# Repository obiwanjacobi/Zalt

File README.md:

# Zalt

Zalt is a home brew Z80 computer with a modern(isch) chipset.

## Zalt Z80 Computer

| Made by Marc Jacobi 2016-2020 |
| --- |
| blog: https://jacobielectronix.wordpress.com/category/zalt/
| email: obiwanjacobi@hotmail.com

<br/>

| Modules: | |
| --- | --- |
| CPU Board | (v1.0) |
| Decoder Board | (v1.0) |
| BusSpy Board | (no pcb) |

<br/>

| Folders: |   |
| --- | --- |
| BusSpy Board | module (handwired)
| CPU Board v1.0 - locked | module (in production)
| Decoder Board v1.0 - locked | module (in production)
| VDP Board v1.0 - locked | module (in production)
| Design | braindump and design documents
| Kicad | Zalt specific (shared) libraries
| Kicad/Board Template | PCB template for stackable boards.
| Kicad/Logical Design | Logical scratch pad for working on ideas.
| Source | Zalt OS source code
| Source/Jacobi.Zalt.IntegrationTests | Zim80 tests
| Source/SystemController | PSoC5 project and source code
| Source/Z80 Tests | Location for all kinds of test code
| Source/Zalt Bios | The Zalt OS source code (to be moved)
| Source/z88dk target | Source for the z88dk Zalt target
| Under Construction/GPU Board v0.1 | Graphics based on a ARM MCU
| Under Construction/TTL VGA v.01 | Graphics with TTL/GAL 1st prototype (partially build)
| Under Construction/TTL VGA v.02 | Graphics with TTL/GAL 2nd prototype
| Under Construction/ZaltToISA | PC ISA interfacing

<br/>

Disclaimer: Only at a very basic level does any of the BIOS code work - see tests. A lot of the source code is still being developed (and changed).

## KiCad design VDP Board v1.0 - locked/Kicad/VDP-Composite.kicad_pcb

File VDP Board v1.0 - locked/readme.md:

# Zalt Video and Audio

This Board contains the V9958 (video) and a YM2149 (sound) vintage chips.
It contains the full set of DRAMs for the V9958, that is a VRAM of 128kB and an extra 64kB extension.

The video signals are available on an IDC connector with grounds separating each signal. RGB and Composite video as well as Chroma and Luma (s-video) signals are present. Note that this is not VGA! Also the stereo Audio is available on this connector.

The YM2149 generates 3 channels of sound which are mixed into a stereo audio output. It also exposes 2 8-bit IO-ports which are brought out on the Audio/Video header.

In addition the board contains a register to hold an RST instruction for Interrupt Mode 0 or an Interrupt Vector for Mode 2 that can be set in software and is put on the bus when an interrupt acknowledge is detected. A jumper can be switched to enable/disable (for IM1 for instance) this option. The interrupt is optionally generated by the V9958.

## TODO

- Too late: I probably need the `INT` signal from the V9958 in the GAL to decide if to handle the the interrupt and (optionally) put the vector on the bus. 1 bodge-wire should fix that. There is still a potential issue with the existing code in the System Controller that also handles interrupts.

## Credits

All credits for the schematic go to these projects.

The V9958 circuit has been copied from the MSX clone project Omega.
https://github.com/skiselev/omega

The YM2149 circuit was copied from this YM2149 for the RC2014 project. https://github.com/electrified/rc2014-ym2149
(although I only used the channel mixing resistors)

## Resources

V9938 Programming Guide (pdf)

Several articles on VDP programming and sources: 
http://map.grauw.nl/articles/vdp_tut.php
http://map.grauw.nl/sources/vdp_rout.php

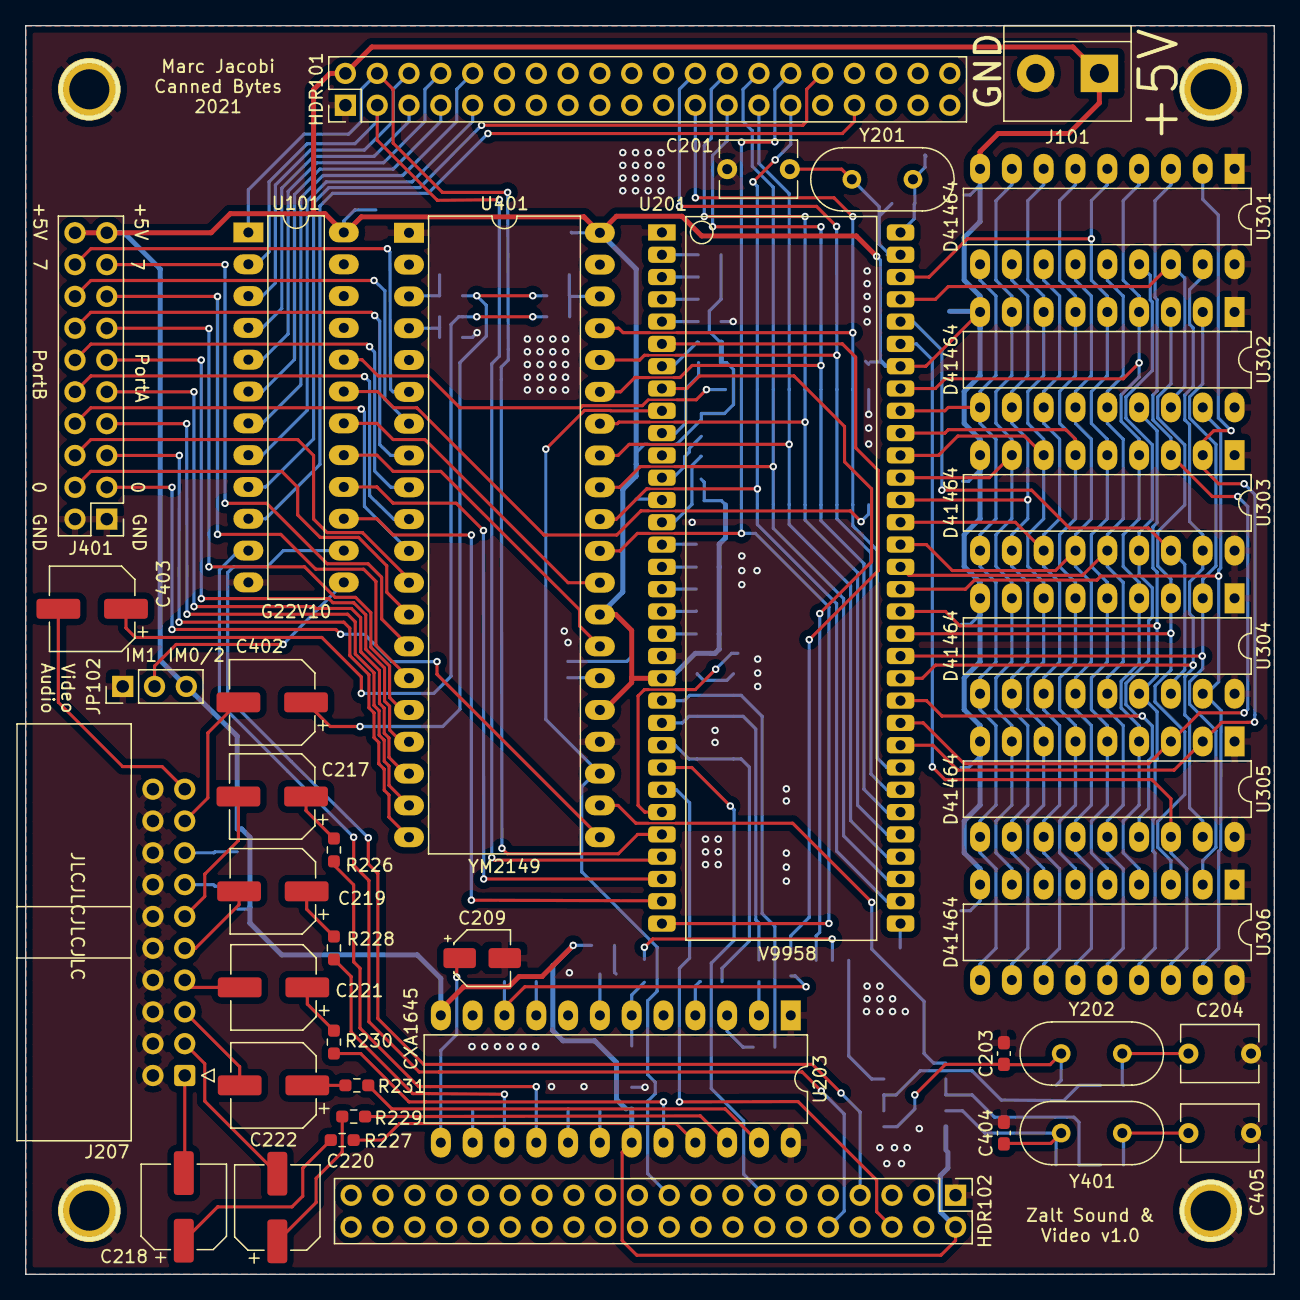
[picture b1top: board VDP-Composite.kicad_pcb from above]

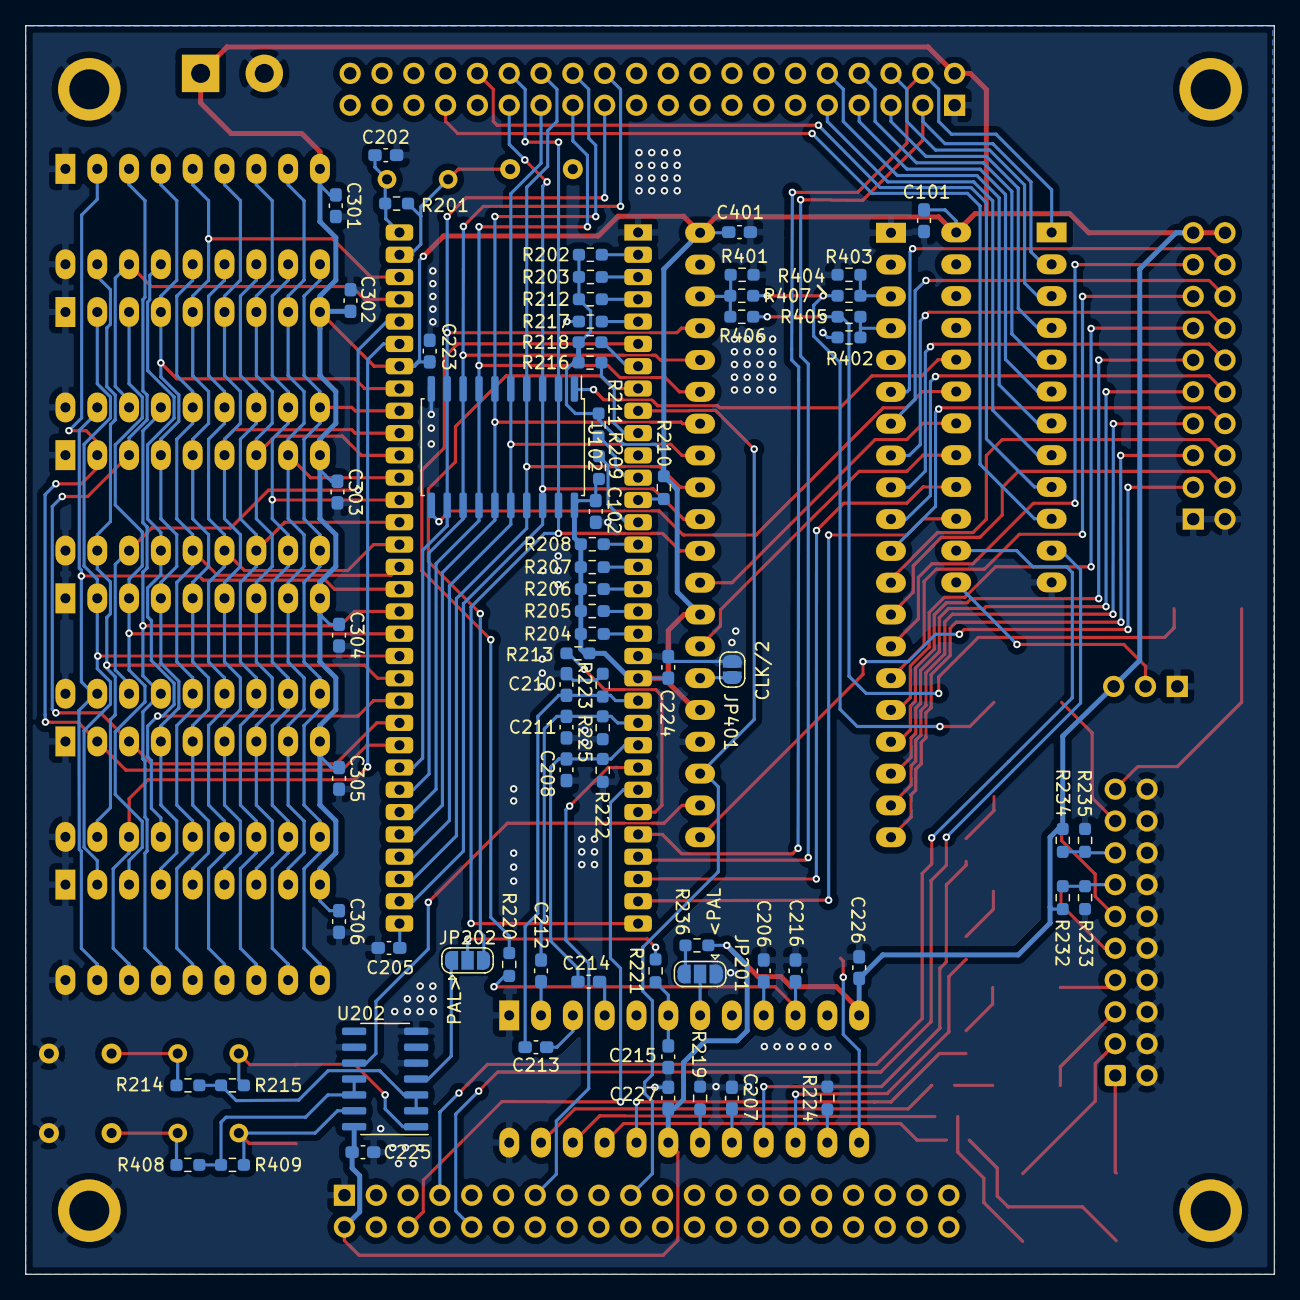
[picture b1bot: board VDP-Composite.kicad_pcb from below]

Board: 2 copper layers, 99.7 x 99.7 mm, 113 parts (70 on the bottom side), 141 nets.

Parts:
1PIN, 1PIN#2, 1PIN#3, 1PIN#4: P***; 1pin
C101, C102, C205, C206, C208, C210, C211, C212, C213, C214, C223, C224, C225, C226, C227, C301, C302, C303, C304, C305, C306, C401: 100nF; C_0603_1608Metric_Pad1.08x0.95mm_HandSolder
C201, C204, C405: 30pF; C_Disc_D6.0mm_W4.4mm_P5.00mm
C202, C203, C404: 22pF; C_0603_1608Metric_Pad1.08x0.95mm_HandSolder
C207: *27/18pF; C_0603_1608Metric_Pad1.08x0.95mm_HandSolder
C209: 10uF; CP_Elec_4x3
C215: 4.7pF; C_0603_1608Metric_Pad1.08x0.95mm_HandSolder
C216: 47pF; C_0603_1608Metric_Pad1.08x0.95mm_HandSolder
C217, C218, C219, C220, C221, C222, C402, C403: 220uF; CP_Elec_6.3x7.7
HDR101: BUSHDR-A; PinHeader_2x20_P2.54mm_Vertical
HDR102: BUSHDR-B; PinHeader_2x20_P2.54mm_Vertical
J101: Power +5V; TerminalBlock_bornier-2_P5.08mm
J207: AVConn; IDC-Header_2x10_P2.54mm_Horizontal
J401: Ports; PinHeader_2x10_P2.54mm_Vertical
JP102: EnableIM; PinHeader_1x03_P2.54mm_Vertical
JP201, JP202: NTSC/PAL; SolderJumper-3_P1.3mm_Open_RoundedPad1.0x1.5mm
JP401: Clock/2; SolderJumper-2_P1.3mm_Open_RoundedPad1.0x1.5mm
R201: 470k; R_0603_1608Metric_Pad0.98x0.95mm_HandSolder
R202, R203, R204, R205, R206, R207, R208, R209, R210, R211, R212, R213, R216, R218, R233: 10k; R_0603_1608Metric_Pad0.98x0.95mm_HandSolder
R214, R220, R232, R236, R406, R407, R408: 1k; R_0603_1608Metric_Pad0.98x0.95mm_HandSolder
R215, R409: 1M; R_0603_1608Metric_Pad0.98x0.95mm_HandSolder
R217, R222, R223, R225: 470; R_0603_1608Metric_Pad0.98x0.95mm_HandSolder
R219: *20/16k; R_0603_1608Metric_Pad0.98x0.95mm_HandSolder
R221: 2.2k; R_0603_1608Metric_Pad0.98x0.95mm_HandSolder
R224: 47k; R_0603_1608Metric_Pad0.98x0.95mm_HandSolder
R226, R227, R228, R229, R230, R231: 75; R_0603_1608Metric_Pad0.98x0.95mm_HandSolder
R234: 120; R_0603_1608Metric_Pad0.98x0.95mm_HandSolder
R235: 180; R_0603_1608Metric_Pad0.98x0.95mm_HandSolder
R401, R402, R403: 3k; R_0603_1608Metric_Pad0.98x0.95mm_HandSolder
R404, R405: 1k6; R_0603_1608Metric_Pad0.98x0.95mm_HandSolder
U101: G22V10; DIP-24_W7.62mm_LongPads
U102: 74HCT574; SOIC-20W_7.5x12.8mm_P1.27mm
U201: V9958; DIP-64_1.78mm_W19.05mm
U202: 74HCT04; SOIC-14_3.9x8.7mm_P1.27mm
U203: CXA1645; DIP-24_W10.16mm_LongPads
U301, U302, U303, U304, U305, U306: D41464; DIP-18_W7.62mm_LongPads
U401: YM2149; DIP-40_W15.24mm_LongPads
Y201: 21.47727MHz; Crystal_HC49-4H_Vertical
Y202: 4.433618MHz; Crystal_HC49-4H_Vertical
Y401: 2-4MHz; Crystal_HC49-4H_Vertical

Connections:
+5V: C101.1, C102.1, C223.1, C224.1, C225.1, C226.1, C227.1, C301.1, C302.1, C303.1, C304.1, C305.1, C306.1, C401.2, HDR101.2, HDR102.2, J101.1, J401.19, J401.20, JP102.3, R202.1, R203.1, R204.1, R205.1, R206.1, R207.1, R208.1, R209.1, R210.1, R211.1, R212.1, R213.1, R216.1, R218.1, R232.1, R234.1, R236.1, U101.24, U102.20, U201.21, U201.58, U202.14, U203.12, U203.19, U301.9, U302.9, U303.9, U304.9, U305.9, U306.9, U401.25, U401.28, U401.40
/A0: HDR101.3, U101.2, U201.29
/A1: HDR101.4, U101.1, U201.28
/A2: HDR101.5, U101.4
/A3: HDR101.6, U101.3
/A4: HDR101.7, U101.6
/A5: HDR101.8, U101.5
/A6: HDR101.9, U101.8
/A7: HDR101.10, U101.7
/BC1: U101.18, U401.29
/BDIR: U101.17, U401.27
/D0: HDR101.23, U102.9, U102.12, U201.40, U401.37
/D1: HDR101.24, U102.8, U102.13, U201.39, U401.36
/D2: HDR101.25, U102.7, U102.14, U201.38, U401.35
/D3: HDR101.26, U102.6, U102.15, U201.37, U401.34
/D4: HDR101.27, U102.5, U102.16, U201.36, U401.33
/D5: HDR101.28, U102.4, U102.17, U201.35, U401.32
/D6: HDR101.29, U102.3, U102.18, U201.34, U401.31
/D7: HDR101.30, U102.2, U102.19, U201.32, U401.30
/IVL: U101.19, U102.11
/SoundGen/A: R403.2, R404.2, U401.3
/SoundGen/AudioL: C402.2, J207.17
/SoundGen/AudioR: C403.2, J207.19
/SoundGen/B: R402.2, R405.2, U401.4
/SoundGen/C: R401.2, R406.2, R407.2, U401.38
/SoundGen/CLK: U202.10, U401.22
/VDP/AV: J207.13, R232.2, R233.1
/VDP/BLUE: C222.2, J207.5
/VDP/Bin: C208.1, C214.2, R222.1, U201.24
/VDP/Bout: C214.1, U203.4
/VDP/CAR-NTSC: JP202.3, U201.8
/VDP/CAR-PAL: JP202.1, U202.4
/VDP/CARout: C215.1, R221.2, U203.6
/VDP/CHROMA: C219.2, J207.9
/VDP/COMP: C221.2, J207.7
/VDP/GREEN: C220.2, J207.3
/VDP/Gin: C210.1, C213.2, R223.1, U201.22
/VDP/Gout: C213.1, U203.3
/VDP/LUMA: C217.2, J207.11
/VDP/RED: C218.2, J207.1
/VDP/Rin: C211.1, C212.2, R225.1, U201.23
/VDP/Rout: C212.1, U203.2
/VDP/SYNCin: R220.1, U201.6
/VDP/SYNCout: C216.1, R220.2, U203.10
/VDP/VRAM/AD0: U201.49, U301.14, U302.14, U303.14, U304.14, U305.14, U306.14
/VDP/VRAM/AD1: U201.50, U301.13, U302.13, U303.13, U304.13, U305.13, U306.13
/VDP/VRAM/AD2: U201.51, U301.12, U302.12, U303.12, U304.12, U305.12, U306.12
/VDP/VRAM/AD3: U201.52, U301.11, U302.11, U303.11, U304.11, U305.11, U306.11
/VDP/VRAM/AD4: U201.53, U301.8, U302.8, U303.8, U304.8, U305.8, U306.8
/VDP/VRAM/AD5: U201.54, U301.7, U302.7, U303.7, U304.7, U305.7, U306.7
/VDP/VRAM/AD6: U201.55, U301.6, U302.6, U303.6, U304.6, U305.6, U306.6
/VDP/VRAM/AD7: U201.56, U301.10, U302.10, U303.10, U304.10, U305.10, U306.10
/VDP/VRAM/RD0: U201.41, U301.2, U303.2, U305.2
/VDP/VRAM/RD1: U201.42, U301.3, U303.3, U305.3
/VDP/VRAM/RD2: U201.43, U301.15, U303.15, U305.15
/VDP/VRAM/RD3: U201.44, U301.17, U303.17, U305.17
/VDP/VRAM/RD4: U201.45, U302.2, U304.2, U306.2
/VDP/VRAM/RD5: U201.46, U302.3, U304.3, U306.3
/VDP/VRAM/RD6: U201.47, U302.15, U304.15, U306.15
/VDP/VRAM/RD7: U201.48, U302.17, U304.17, U306.17
/VDP/VRAM/R~W: U201.57, U301.4, U302.4, U303.4, U304.4, U305.4, U306.4
/VDP/VRAM/~CAS1: U201.61, U301.16, U302.16
/VDP/VRAM/~CAS2: U201.60, U303.16, U304.16
/VDP/VRAM/~CASx: U201.59, U305.16, U306.16
/VDP/VRAM/~RAS: U201.62, U301.5, U302.5, U303.5, U304.5, U305.5, U306.5
/VDP/YS: J207.15, R234.2, R235.1
/~INT: HDR102.13, U201.25
/~IOREQ: HDR102.10, U101.11
/~IVOE: U101.20, U102.1
/~M1: HDR102.7, U101.14
/~RD: HDR101.33, U101.10
/~RST: HDR102.19, U201.9, U401.23
/~VDP_RD: U101.15, U201.31
/~VDP_WR: U101.16, U201.30
/~WAIT: HDR102.6, U201.26
/~WR: HDR101.32, U101.9
GND: 1PIN.1, 1PIN#2.1, 1PIN#3.1, 1PIN#4.1, C101.2, C102.2, C201.2, C202.2, C203.2, C204.2, C205.2, C206.2, C207.2, C208.2, C209.2, C210.2, C211.2, C215.2, C216.2, C223.2, C224.2, C225.2, C226.2, C227.2, C301.2, C302.2, C303.2, C304.2, C305.2, C306.2, C401.1, C404.2, C405.2, HDR101.1, HDR102.1, J101.2, J207.2, J207.4, J207.6, J207.8, J207.10, J207.12, J207.14, J207.16, J207.18, J207.20, J401.1, J401.2, JP102.1, JP201.1, JP401.1, R217.2, R219.2, R222.2, R223.2, R224.2, R225.2, R233.2, R235.2, R401.1, R402.1, R403.1, U101.12, U102.10, U201.1, U201.20, U202.5, U202.7, U202.9, U203.1, U203.24, U301.1, U301.18, U302.1, U302.18, U303.1, U303.18, U304.1, U304.18, U305.1, U305.18, U306.1, U306.18, U401.1, U401.24
unnamed: C201.1, R201.1, U201.63, Y201.1
unnamed: C202.1, R201.2, U201.64, Y201.2
unnamed: C203.1, R215.1, U202.1, Y202.1
unnamed: C204.1, R214.2, Y202.2
unnamed: C205.1, U201.33
unnamed: C206.1, U203.9
unnamed: C207.1, U203.17
unnamed: C209.1, U203.13
unnamed: C217.1, R226.2
unnamed: C218.1, R227.2
unnamed: C219.1, R228.2
unnamed: C220.1, R229.2
unnamed: C221.1, R230.2
unnamed: C222.1, R231.2
unnamed: C402.1, R404.1, R407.1
unnamed: C403.1, R405.1, R406.1
unnamed: C404.1, R409.1, U202.13, Y401.1
unnamed: C405.1, R408.2, Y401.2
unnamed: J401.3, U401.21
unnamed: J401.4, U401.13
unnamed: J401.5, U401.20
unnamed: J401.6, U401.12
unnamed: J401.7, U401.19
unnamed: J401.8, U401.11
unnamed: J401.9, U401.18
unnamed: J401.10, U401.10
unnamed: J401.11, U401.17
unnamed: J401.12, U401.9
unnamed: J401.13, U401.16
unnamed: J401.14, U401.8
unnamed: J401.15, U401.15
unnamed: J401.16, U401.7
unnamed: J401.17, U401.14
unnamed: J401.18, U401.6
unnamed: JP102.2, U101.13
unnamed: JP201.2, U203.7
unnamed: JP201.3, R236.2
unnamed: JP202.2, R221.1
unnamed: JP401.2, U401.26
unnamed: R202.2, U201.2
unnamed: R203.2, U201.3
unnamed: R204.2, U201.19
unnamed: R205.2, U201.18
unnamed: R206.2, U201.17
unnamed: R207.2, U201.16
unnamed: R208.2, U201.15
unnamed: R209.2, U201.14
unnamed: R210.2, U201.13
unnamed: R211.2, U201.12
unnamed: R212.2, U201.4
unnamed: R213.2, U201.27
unnamed: R214.1, R215.2, U202.2, U202.3
unnamed: R216.2, U201.10
unnamed: R217.1, U201.5
unnamed: R218.2, U201.7
unnamed: R219.1, U203.18
unnamed: R224.1, U203.14
unnamed: R226.1, U203.16
unnamed: R227.1, U203.21
unnamed: R228.1, U203.15
unnamed: R229.1, U203.22
unnamed: R230.1, U203.20
unnamed: R231.1, U203.23
unnamed: R408.1, R409.2, U202.11, U202.12

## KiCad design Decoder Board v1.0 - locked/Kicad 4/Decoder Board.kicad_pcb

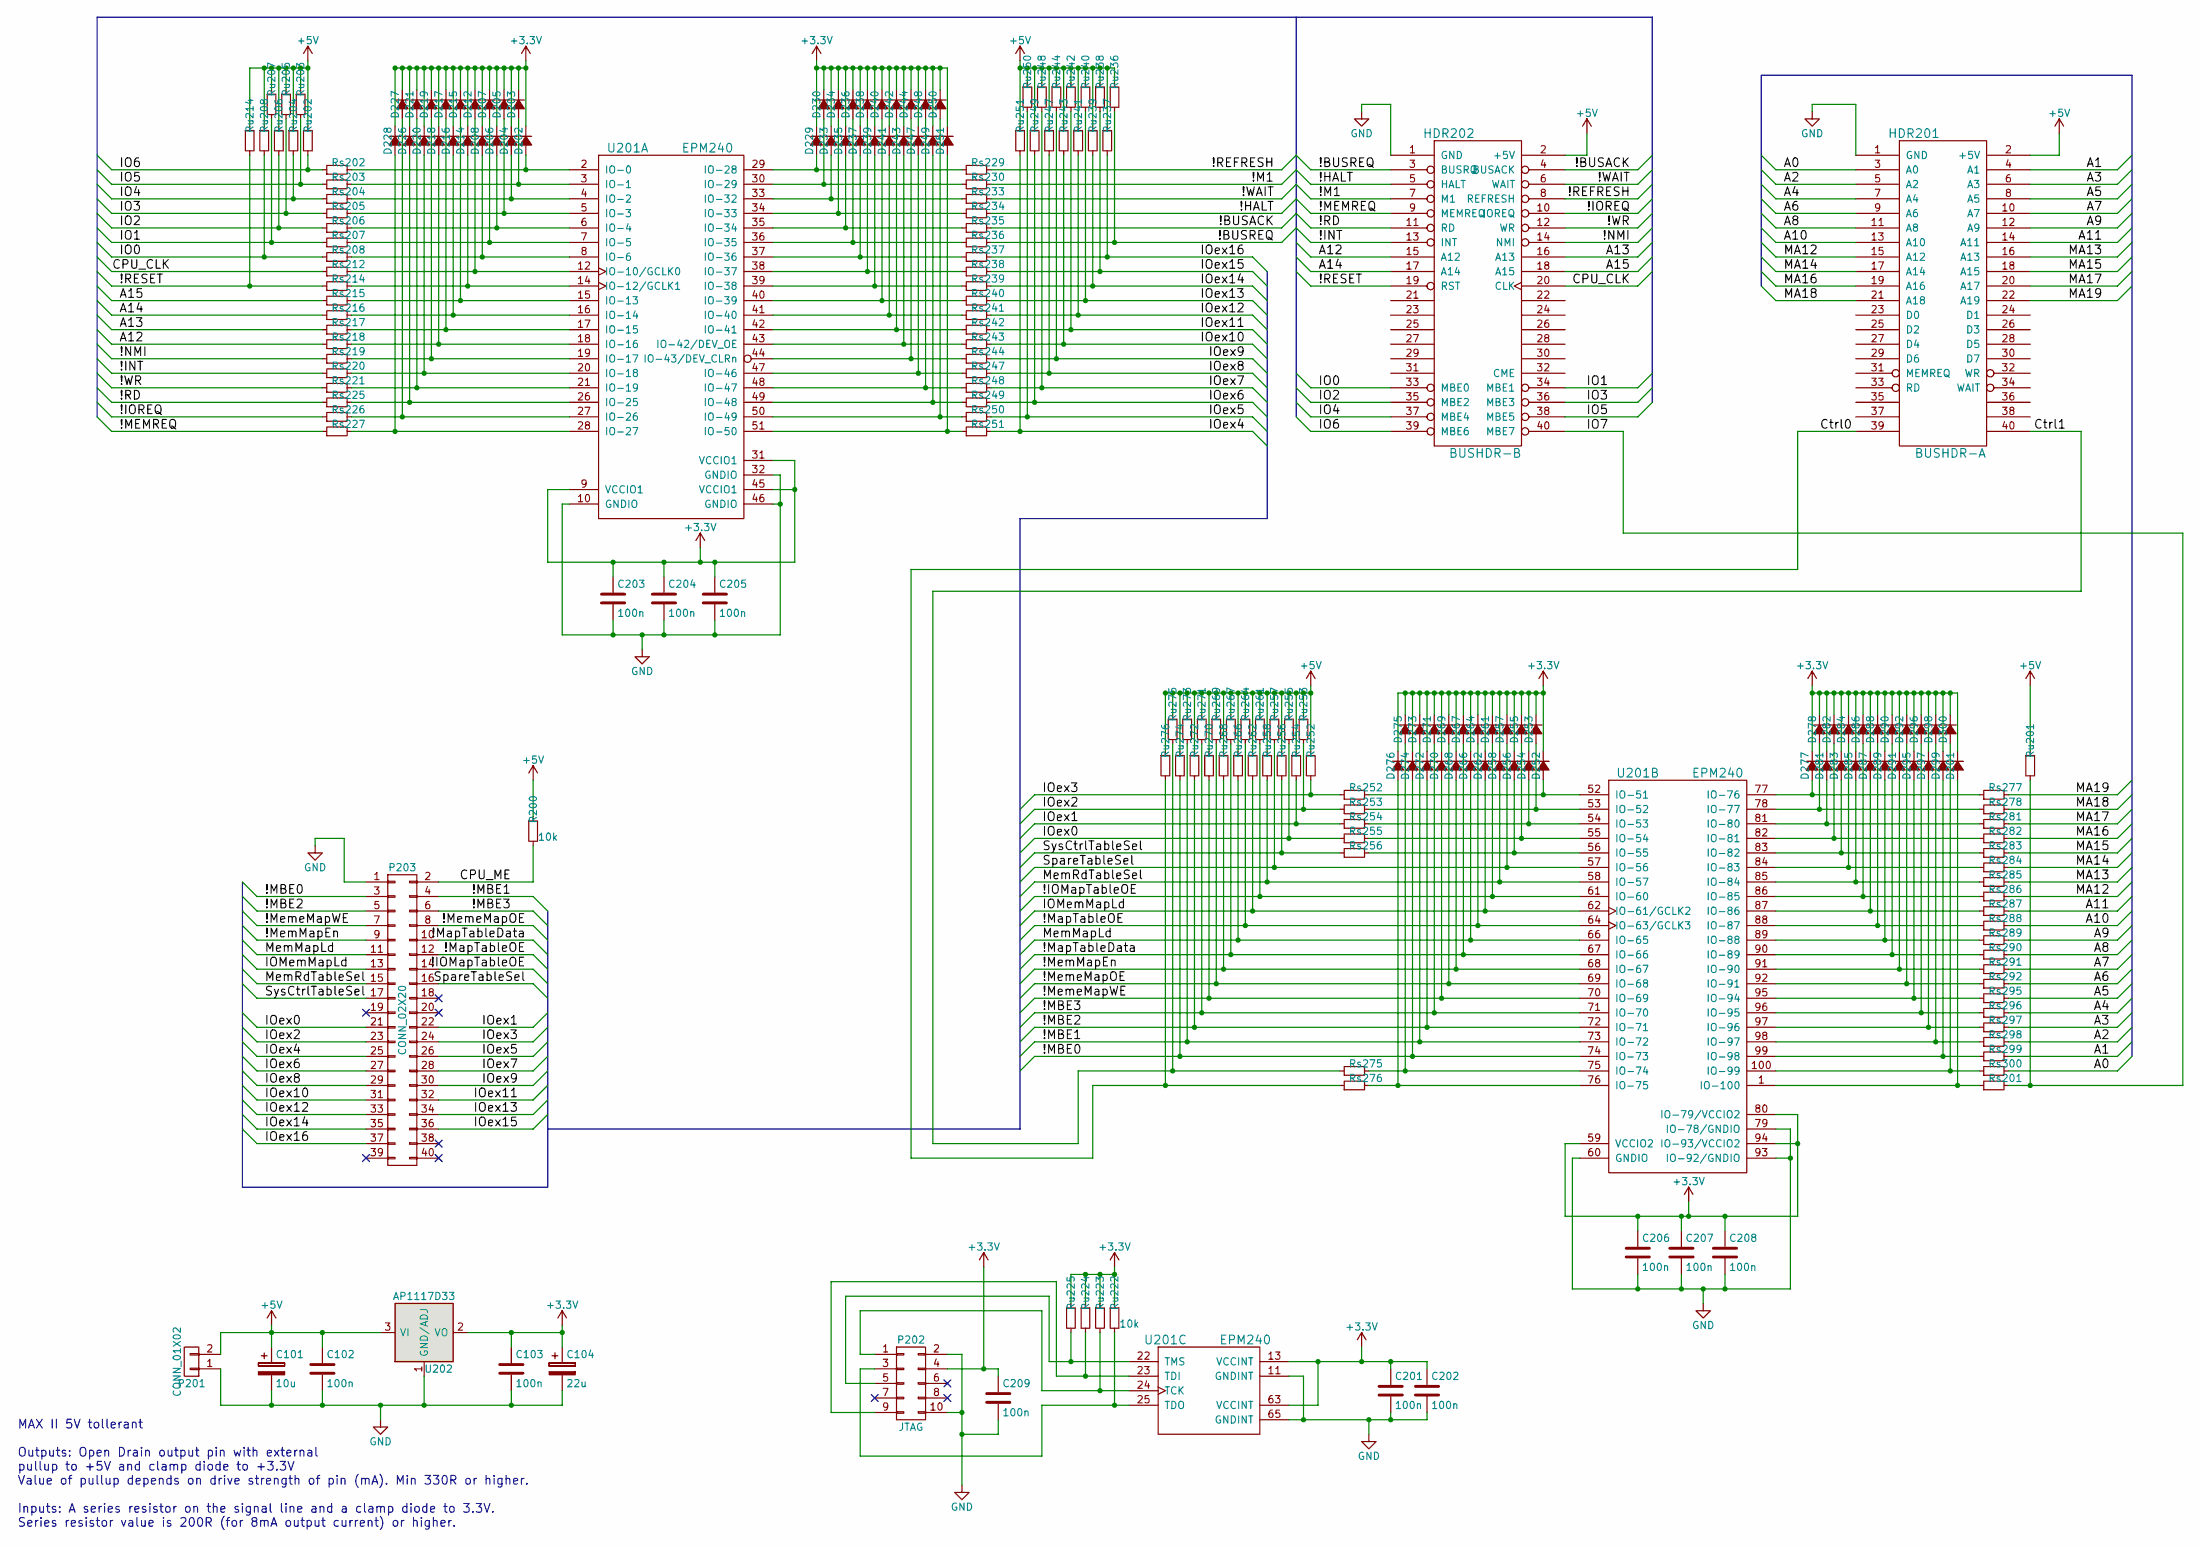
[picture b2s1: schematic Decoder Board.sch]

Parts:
C101: 10u; TantalC_SizeC_EIA-6032_HandSoldering
C102, C103, C201, C202, C203, C204, C205, C206, C207, C208, C209: 100n; C_0603_HandSoldering
C104: 22u; TantalC_SizeC_EIA-6032_HandSoldering
D201, D202, D203, D204, D205, D206, D207, D208, D212, D214, D215, D216, D217, D218, D219, D220, D221, D226, D227, D228, D229, D230, D233, D234, D235, D236, D237, D238, D239, D240, D241, D242, D243, D244, D247, D248, D249, D250, D251, D252, D253, D254, D255, D256, D257, D258, D261, D262, D264, D266, D267, D268, D269, D270, D271, D272, D273, D274, D275, D276, D277, D278, D281, D282, D283, D284, D285, D286, D287, D288, D289, D290, D291, D292, D295, D296, D297, D298, D299, D300: SOD-123
HDR201: BUSHDR-A; IDC_Header_Straight_40pins
HDR202: BUSHDR-B; IDC_Header_Straight_40pins
P201: CONN_01X02; PINHEAD1-2
P202: JTAG; IDC_Header_Straight_10pins
P203: CONN_02X20; IDC_Header_Straight_40pins
R200: 10k; R_0603_HandSoldering
Rs201, Rs202, Rs203, Rs204, Rs205, Rs206, Rs207, Rs208, Rs212, Rs214, Rs215, Rs216, Rs217, Rs218, Rs219, Rs220, Rs221, Rs225, Rs226, Rs227, Rs229, Rs230, Rs233, Rs234, Rs235, Rs236, Rs237, Rs238, Rs239, Rs240, Rs241, Rs242, Rs243, Rs244, Rs247, Rs248, Rs249, Rs250, Rs251, Rs252, Rs253, Rs254, Rs255, Rs256, Rs275, Rs276, Rs277, Rs278, Rs281, Rs282, Rs283, Rs284, Rs285, Rs286, Rs287, Rs288, Rs289, Rs290, Rs291, Rs292, Rs295, Rs296, Rs297, Rs298, Rs299, Rs300: R_0603_HandSoldering
Ru201, Ru202, Ru203, Ru204, Ru205, Ru206, Ru207, Ru208, Ru214, Ru223, Ru224, Ru225, Ru236, Ru237, Ru238, Ru239, Ru240, Ru241, Ru242, Ru243, Ru244, Ru247, Ru248, Ru249, Ru250, Ru251, Ru252, Ru253, Ru254, Ru255, Ru256, Ru257, Ru258, Ru261, Ru262, Ru264, Ru266, Ru267, Ru268, Ru269, Ru270, Ru271, Ru272, Ru273, Ru274, Ru275, Ru276: R_0603_HandSoldering
Ru222: 10k; R_0603_HandSoldering
U201: EPM240; LQFP-100_14x14mm_Pitch0.5mm
U202: AP1117D33; SOT89-3_Housing_Handsoldering

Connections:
+3V3: C103.1, C104.1, C201.1, C202.1, C203.1, C204.1, C205.1, C206.1, C207.1, C208.1, C209.1, D201.1 (K), D202.1 (K), D203.1 (K), D204.1 (K), D205.1 (K), D206.1 (K), D207.1 (K), D208.1 (K), D212.1 (K), D214.1 (K), D215.1 (K), D216.1 (K), D217.1 (K), D218.1 (K), D219.1 (K), D220.1 (K), D221.1 (K), D226.1 (K), D227.1 (K), D228.1 (K), D229.1 (K), D230.1 (K), D233.1 (K), D234.1 (K), D235.1 (K), D236.1 (K), D237.1 (K), D238.1 (K), D239.1 (K), D240.1 (K), D241.1 (K), D242.1 (K), D243.1 (K), D244.1 (K), D247.1 (K), D248.1 (K), D249.1 (K), D250.1 (K), D251.1 (K), D252.1 (K), D253.1 (K), D254.1 (K), D255.1 (K), D256.1 (K), D257.1 (K), D258.1 (K), D261.1 (K), D262.1 (K), D264.1 (K), D266.1 (K), D267.1 (K), D268.1 (K), D269.1 (K), D270.1 (K), D271.1 (K), D272.1 (K), D273.1 (K), D274.1 (K), D275.1 (K), D276.1 (K), D277.1 (K), D278.1 (K), D281.1 (K), D282.1 (K), D283.1 (K), D284.1 (K), D285.1 (K), D286.1 (K), D287.1 (K), D288.1 (K), D289.1 (K), D290.1 (K), D291.1 (K), D292.1 (K), D295.1 (K), D296.1 (K), D297.1 (K), D298.1 (K), D299.1 (K), D300.1 (K), P202.4, Ru222.1, Ru223.1, Ru224.1, Ru225.1, U201.9 (VCCIO1), U201.13 (VCCINT), U201.31 (VCCIO1), U201.45 (VCCIO1), U201.59 (VCCIO2), U201.63 (VCCINT), U201.80 (IO-79/VCCIO2), U201.94 (IO-93/VCCIO2), U202.2 (VO)
+5V: C101.1, C102.1, HDR201.2 (+5V), HDR202.2 (+5V), P201.2, R200.1, Ru201.1, Ru202.1, Ru203.1, Ru204.1, Ru205.1, Ru206.1, Ru207.1, Ru208.1, Ru214.1, Ru236.1, Ru237.1, Ru238.1, Ru239.1, Ru240.1, Ru241.1, Ru242.1, Ru243.1, Ru244.1, Ru247.1, Ru248.1, Ru249.1, Ru250.1, Ru251.1, Ru252.1, Ru253.1, Ru254.1, Ru255.1, Ru256.1, Ru257.1, Ru258.1, Ru261.1, Ru262.1, Ru264.1, Ru266.1, Ru267.1, Ru268.1, Ru269.1, Ru270.1, Ru271.1, Ru272.1, Ru273.1, Ru274.1, Ru275.1, Ru276.1, U202.3 (VI)
/!BUSACK: HDR202.4 (BUSACK), Rs235.2
/!BUSREQ: HDR202.3 (BUSRQ), Rs236.2, Ru236.2
/!HALT: HDR202.5 (HALT), Rs234.2
/!INT: HDR202.13 (INT), Rs220.1
/!IOMapTableOE: D261.2 (A), P203.14, Ru261.2, U201.61 (IO-60)
/!IOREQ: HDR202.10 (IOREQ), Rs226.1
/!M1: HDR202.7 (M1), Rs230.2
/!MBE0: D274.2 (A), P203.3, Ru274.2, U201.74 (IO-73)
/!MBE1: D273.2 (A), P203.4, Ru273.2, U201.73 (IO-72)
/!MBE2: D272.2 (A), P203.5, Ru272.2, U201.72 (IO-71)
/!MBE3: D271.2 (A), P203.6, Ru271.2, U201.71 (IO-70)
/!MEMREQ: HDR202.9 (MEMREQ), Rs227.1
/!MapTableData: D267.2 (A), P203.10, Ru267.2, U201.67 (IO-66)
/!MapTableOE: D264.2 (A), P203.12, Ru264.2, U201.64 (IO-63/GCLK3)
/!MemMapWE: D268.2 (A), P203.9, Ru268.2, U201.68 (IO-67)
/!MemeMapEn: D270.2 (A), P203.7, Ru270.2, U201.70 (IO-69)
/!MemeMapOE: D269.2 (A), P203.8, Ru269.2, U201.69 (IO-68)
/!NMI: HDR202.14 (NMI), Rs219.1
/!RD: HDR202.11 (RD), Rs225.1
/!REFRESH: HDR202.8 (REFRESH), Rs229.2
/!RESET: HDR202.19 (RST), Rs214.1, Ru214.2
/!WAIT: HDR202.6 (WAIT), Rs233.2
/!WR: HDR202.12 (WR), Rs221.1
/A0: HDR201.3 (A0), Rs300.2
/A1: HDR201.4 (A1), Rs299.2
/A2: HDR201.5 (A2), Rs298.2
/A3: HDR201.6 (A3), Rs297.2
/A4: HDR201.7 (A4), Rs296.2
/A5: HDR201.8 (A5), Rs295.2
/A6: HDR201.9 (A6), Rs292.2
/A7: HDR201.10 (A7), Rs291.2
/A8: HDR201.11 (A8), Rs290.2
/A9: HDR201.12 (A9), Rs289.2
/A10: HDR201.13 (A10), Rs288.2
/A11: HDR201.14 (A11), Rs287.2
/A12: HDR202.15 (A12), Rs218.1
/A13: HDR202.16 (A13), Rs217.1
/A14: HDR202.17 (A14), Rs216.1
/A15: HDR202.18 (A15), Rs215.1
/CPU_CLK: HDR202.20 (CLK), Rs212.1
/CPU_ME: P203.2, R200.2
/Ctrl0: HDR201.39, Rs276.1, Ru276.2
/Ctrl1: HDR201.40, Rs275.1, Ru275.2
/IO0: HDR202.33 (MBE0), Rs208.1, Ru208.2
/IO1: HDR202.34 (MBE1), Rs207.1, Ru207.2
/IO2: HDR202.35 (MBE2), Rs206.1, Ru206.2
/IO3: HDR202.36 (MBE3), Rs205.1, Ru205.2
/IO4: HDR202.37 (MBE4), Rs204.1, Ru204.2
/IO5: HDR202.38 (MBE5), Rs203.1, Ru203.2
/IO6: HDR202.39 (MBE6), Rs202.1, Ru202.2
/IO7: HDR202.40 (MBE7), Rs201.2, Ru201.2
/IOMemMapLd: D262.2 (A), P203.13, Ru262.2, U201.62 (IO-61/GCLK2)
/IOex0: P203.21, Rs255.1, Ru255.2
/IOex1: P203.22, Rs254.1, Ru254.2
/IOex2: P203.23, Rs253.1, Ru253.2
/IOex3: P203.24, Rs252.1, Ru252.2
/IOex4: P203.25, Rs251.2, Ru251.2
/IOex5: P203.26, Rs250.2, Ru250.2
/IOex6: P203.27, Rs249.2, Ru249.2
/IOex7: P203.28, Rs248.2, Ru248.2
/IOex8: P203.29, Rs247.2, Ru247.2
/IOex9: P203.30, Rs244.2, Ru244.2
/IOex10: P203.31, Rs243.2, Ru243.2
/IOex11: P203.32, Rs242.2, Ru242.2
/IOex12: P203.33, Rs241.2, Ru241.2
/IOex13: P203.34, Rs240.2, Ru240.2
/IOex14: P203.35, Rs239.2, Ru239.2
/IOex15: P203.36, Rs238.2, Ru238.2
/IOex16: P203.37, Rs237.2, Ru237.2
/MA12: HDR201.15 (A12), Rs286.2
/MA13: HDR201.16 (A13), Rs285.2
/MA14: HDR201.17 (A14), Rs284.2
/MA15: HDR201.18 (A15), Rs283.2
/MA16: HDR201.19 (A16), Rs282.2
/MA17: HDR201.20 (A17), Rs281.2
/MA18: HDR201.21 (A18), Rs278.2
/MA19: HDR201.22 (A19), Rs277.2
/MemMapLd: D266.2 (A), P203.11, Ru266.2, U201.66 (IO-65)
/MemRdTableSel: D258.2 (A), P203.15, Ru258.2, U201.58 (IO-57)
/SpareTableSel: D257.2 (A), P203.16, Ru257.2, U201.57 (IO-56)
/SysCtrlTableSel: P203.17, Rs256.1, Ru256.2
GND: C101.2, C102.2, C103.2, C104.2, C201.2, C202.2, C203.2, C204.2, C205.2, C206.2, C207.2, C208.2, C209.2, HDR201.1 (GND), HDR202.1 (GND), P201.1, P202.2, P202.10, P203.1, U201.10 (GNDIO), U201.11 (GNDINT), U201.32 (GNDIO), U201.46 (GNDIO), U201.60 (GNDIO), U201.65 (GNDINT), U201.79 (IO-78/GNDIO), U201.93 (IO-92/GNDIO), U202.1 (GND/ADJ); also elsewhere on the board
unnamed: D201.2 (A), Rs201.1, U201.1 (IO-100)
unnamed: D202.2 (A), Rs202.2, U201.2 (IO-0)
unnamed: D203.2 (A), Rs203.2, U201.3 (IO-1)
unnamed: D204.2 (A), Rs204.2, U201.4 (IO-2)
unnamed: D205.2 (A), Rs205.2, U201.5 (IO-3)
unnamed: D206.2 (A), Rs206.2, U201.6 (IO-4)
unnamed: D207.2 (A), Rs207.2, U201.7 (IO-5)
unnamed: D208.2 (A), Rs208.2, U201.8 (IO-6)
unnamed: D212.2 (A), Rs212.2, U201.12 (IO-10/GCLK0)
unnamed: D214.2 (A), Rs214.2, U201.14 (IO-12/GCLK1)
unnamed: D215.2 (A), Rs215.2, U201.15 (IO-13)
unnamed: D216.2 (A), Rs216.2, U201.16 (IO-14)
unnamed: D217.2 (A), Rs217.2, U201.17 (IO-15)
unnamed: D218.2 (A), Rs218.2, U201.18 (IO-16)
unnamed: D219.2 (A), Rs219.2, U201.19 (IO-17)
unnamed: D220.2 (A), Rs220.2, U201.20 (IO-18)
unnamed: D221.2 (A), Rs221.2, U201.21 (IO-19)
unnamed: D226.2 (A), Rs225.2, U201.26 (IO-25)
unnamed: D227.2 (A), Rs226.2, U201.27 (IO-26)
unnamed: D228.2 (A), Rs227.2, U201.28 (IO-27)
unnamed: D229.2 (A), Rs229.1, U201.29 (IO-28)
unnamed: D230.2 (A), Rs230.1, U201.30 (IO-29)
unnamed: D233.2 (A), Rs233.1, U201.33 (IO-32)
unnamed: D234.2 (A), Rs234.1, U201.34 (IO-33)
unnamed: D235.2 (A), Rs235.1, U201.35 (IO-34)
unnamed: D236.2 (A), Rs236.1, U201.36 (IO-35)
unnamed: D237.2 (A), Rs237.1, U201.37 (IO-36)
unnamed: D238.2 (A), Rs238.1, U201.38 (IO-37)
unnamed: D239.2 (A), Rs239.1, U201.39 (IO-38)
unnamed: D240.2 (A), Rs240.1, U201.40 (IO-39)
unnamed: D241.2 (A), Rs241.1, U201.41 (IO-40)
unnamed: D242.2 (A), Rs242.1, U201.42 (IO-41)
unnamed: D243.2 (A), Rs243.1, U201.43 (IO-42/DEV_OE)
unnamed: D244.2 (A), Rs244.1, U201.44 (IO-43/DEV_CLRn)
unnamed: D247.2 (A), Rs247.1, U201.47 (IO-46)
unnamed: D248.2 (A), Rs248.1, U201.48 (IO-47)
unnamed: D249.2 (A), Rs249.1, U201.49 (IO-48)
unnamed: D250.2 (A), Rs250.1, U201.50 (IO-49)
unnamed: D251.2 (A), Rs251.1, U201.51 (IO-50)
unnamed: D252.2 (A), Rs252.2, U201.52 (IO-51)
unnamed: D253.2 (A), Rs253.2, U201.53 (IO-52)
unnamed: D254.2 (A), Rs254.2, U201.54 (IO-53)
unnamed: D255.2 (A), Rs255.2, U201.55 (IO-54)
unnamed: D256.2 (A), Rs256.2, U201.56 (IO-55)
unnamed: D275.2 (A), Rs275.2, U201.75 (IO-74)
unnamed: D276.2 (A), Rs276.2, U201.76 (IO-75)
unnamed: D277.2 (A), Rs277.1, U201.77 (IO-76)
unnamed: D278.2 (A), Rs278.1, U201.78 (IO-77)
unnamed: D281.2 (A), Rs281.1, U201.81 (IO-80)
unnamed: D282.2 (A), Rs282.1, U201.82 (IO-81)
unnamed: D283.2 (A), Rs283.1, U201.83 (IO-82)
unnamed: D284.2 (A), Rs284.1, U201.84 (IO-83)
unnamed: D285.2 (A), Rs285.1, U201.85 (IO-84)
unnamed: D286.2 (A), Rs286.1, U201.86 (IO-85)
unnamed: D287.2 (A), Rs287.1, U201.87 (IO-86)
unnamed: D288.2 (A), Rs288.1, U201.88 (IO-87)
unnamed: D289.2 (A), Rs289.1, U201.89 (IO-88)
unnamed: D290.2 (A), Rs290.1, U201.90 (IO-89)
unnamed: D291.2 (A), Rs291.1, U201.91 (IO-90)
unnamed: D292.2 (A), Rs292.1, U201.92 (IO-91)
unnamed: D295.2 (A), Rs295.1, U201.95 (IO-94)
unnamed: D296.2 (A), Rs296.1, U201.96 (IO-95)
unnamed: D297.2 (A), Rs297.1, U201.97 (IO-96)
unnamed: D298.2 (A), Rs298.1, U201.98 (IO-97)
unnamed: D299.2 (A), Rs299.1, U201.99 (IO-98)
unnamed: D300.2 (A), Rs300.1, U201.100 (IO-99)
unnamed: P202.1, Ru223.2, U201.24 (TCK)
unnamed: P202.3, Ru222.2, U201.25 (TDO)
unnamed: P202.5, Ru225.2, U201.22 (TMS)
unnamed: P202.9, Ru224.2, U201.23 (TDI)

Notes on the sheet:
MAX II 5V tollerant Outputs: Open Drain output pin with external pullup to +5V and clamp diode to +3.3V Value of pullup depends on drive strength of pin (mA). Min 330R or higher. Inputs: A series resistor on the signal line and a clamp diode to 3.3V. Series resistor value is 200R (for 8mA output cu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

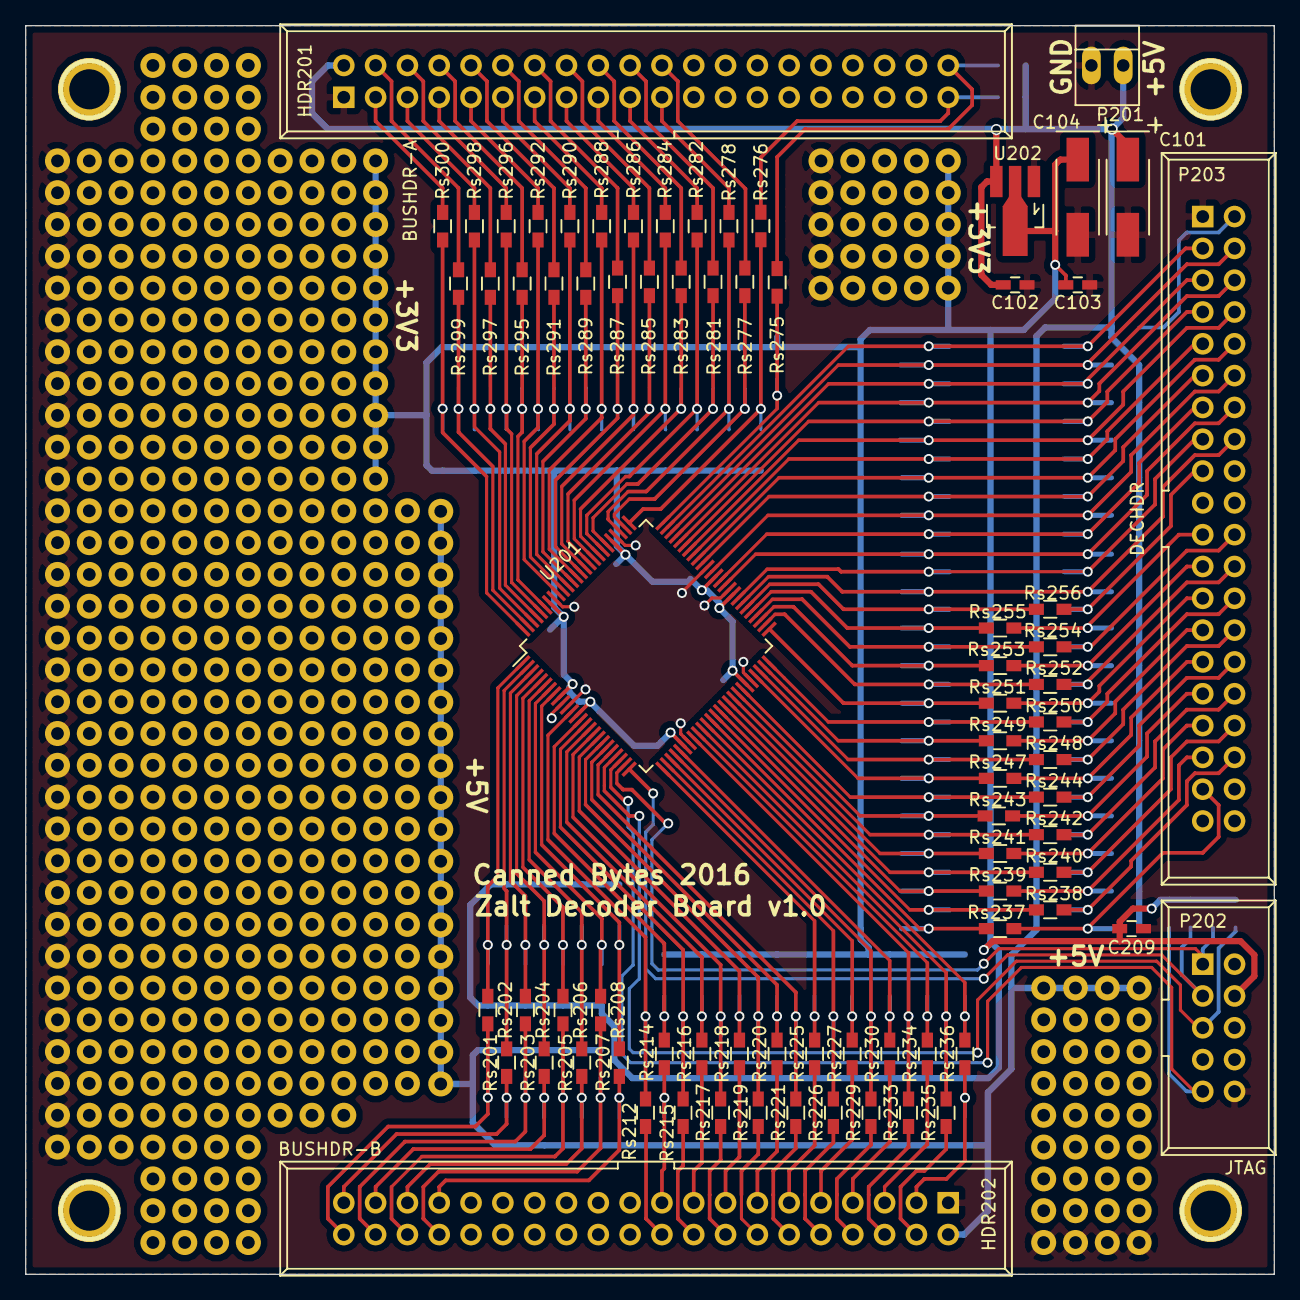
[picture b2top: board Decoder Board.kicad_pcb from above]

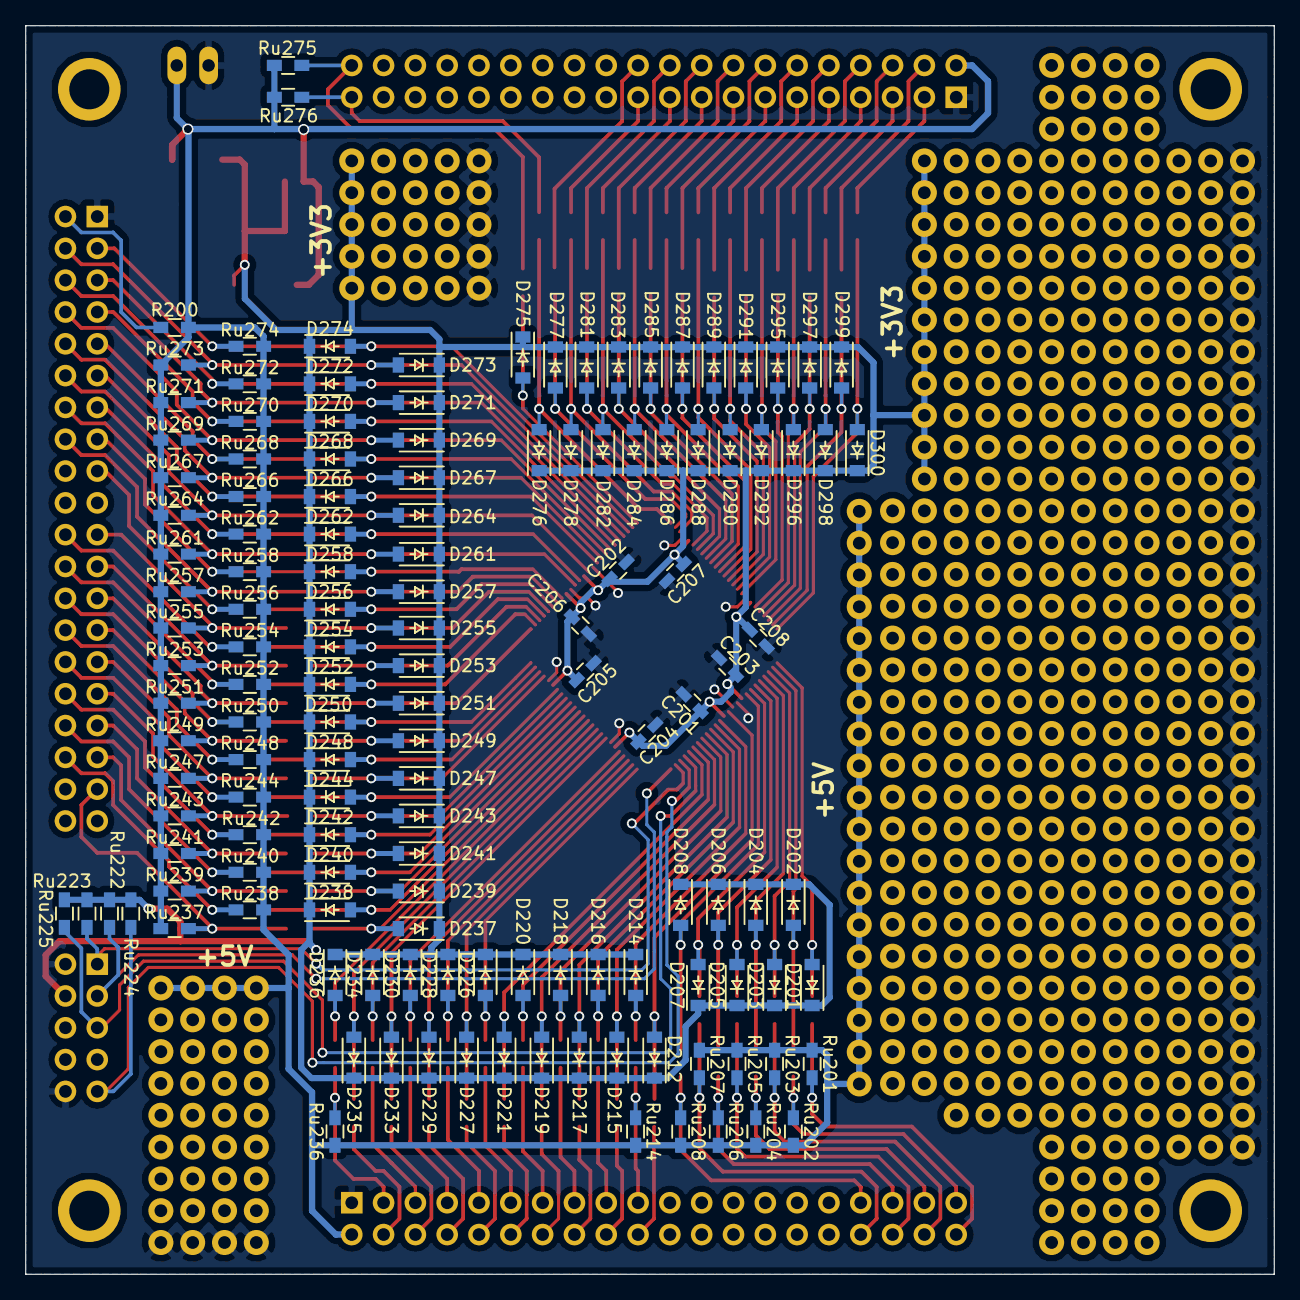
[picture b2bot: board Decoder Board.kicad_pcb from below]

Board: 2 copper layers, 99.7 x 99.7 mm, 219 parts (137 on the bottom side), 154 nets.

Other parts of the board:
1PIN, 1PIN#2, 1PIN#3, 1PIN#4: P***; 1pin

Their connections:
GND: 1PIN.1, 1PIN#2.1, 1PIN#3.1, 1PIN#4.1; also elsewhere on the board
